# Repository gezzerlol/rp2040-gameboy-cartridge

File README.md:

2 layer pcb version of Shilga's RP2040 Gameboy flash cartridge. Also replaced some components with bigger packages, and easier to find components.

Changes:
-Removed inner layers, instead routed buses and tracks in place of the power planes at the back layer. Also one single signal track is moved to the back layer.
-Replaced 1005 caps with 1608's. JLCPCB doesn't do 1005 package in ecomomic PCBA service.
-Added an optional location for AMS1117-3.3 regulator, in case the MCP1825T isn't available. If AMS1117-3.3 is used, JP2 middle pad solder mask should be removed and soldered to supply a constant POWERGOOD signal that enables the level shifters. 

With these three changes, the PCB could be manufactured at 2$ for 5pcs at JLCPCB. Also if PCBA service is needed, it reduces the number of the extended components that add 3$ of setup fee each. 

The RP2040, TXB0108, TXB0102 and the WS2812b are inevitably extended parts at JLCPCB.

Not tested:
-The whole PCB
-JP2 POWERGOOD bypass functionality(keeping IC's enabled at all times may be a problem)
-Replacement of power planes with tracks
-AMS1117-3.3 compatibility

Goals:
-Replacement of TXB level shifters with discrete circuits made of jellybean transistors. This might be difficult because there are 26 data lines that needs to be level shifted and there is little space, too much moving around might be needed. Heck, might even need to use the back layer.
-Replacement of CJ2302 mosfet with a cheaper one. AO3400A might be a candidate.
-Replacement of the diodes with jellybean ones
-Making the whole pcb made of jellybean parts except RP2040

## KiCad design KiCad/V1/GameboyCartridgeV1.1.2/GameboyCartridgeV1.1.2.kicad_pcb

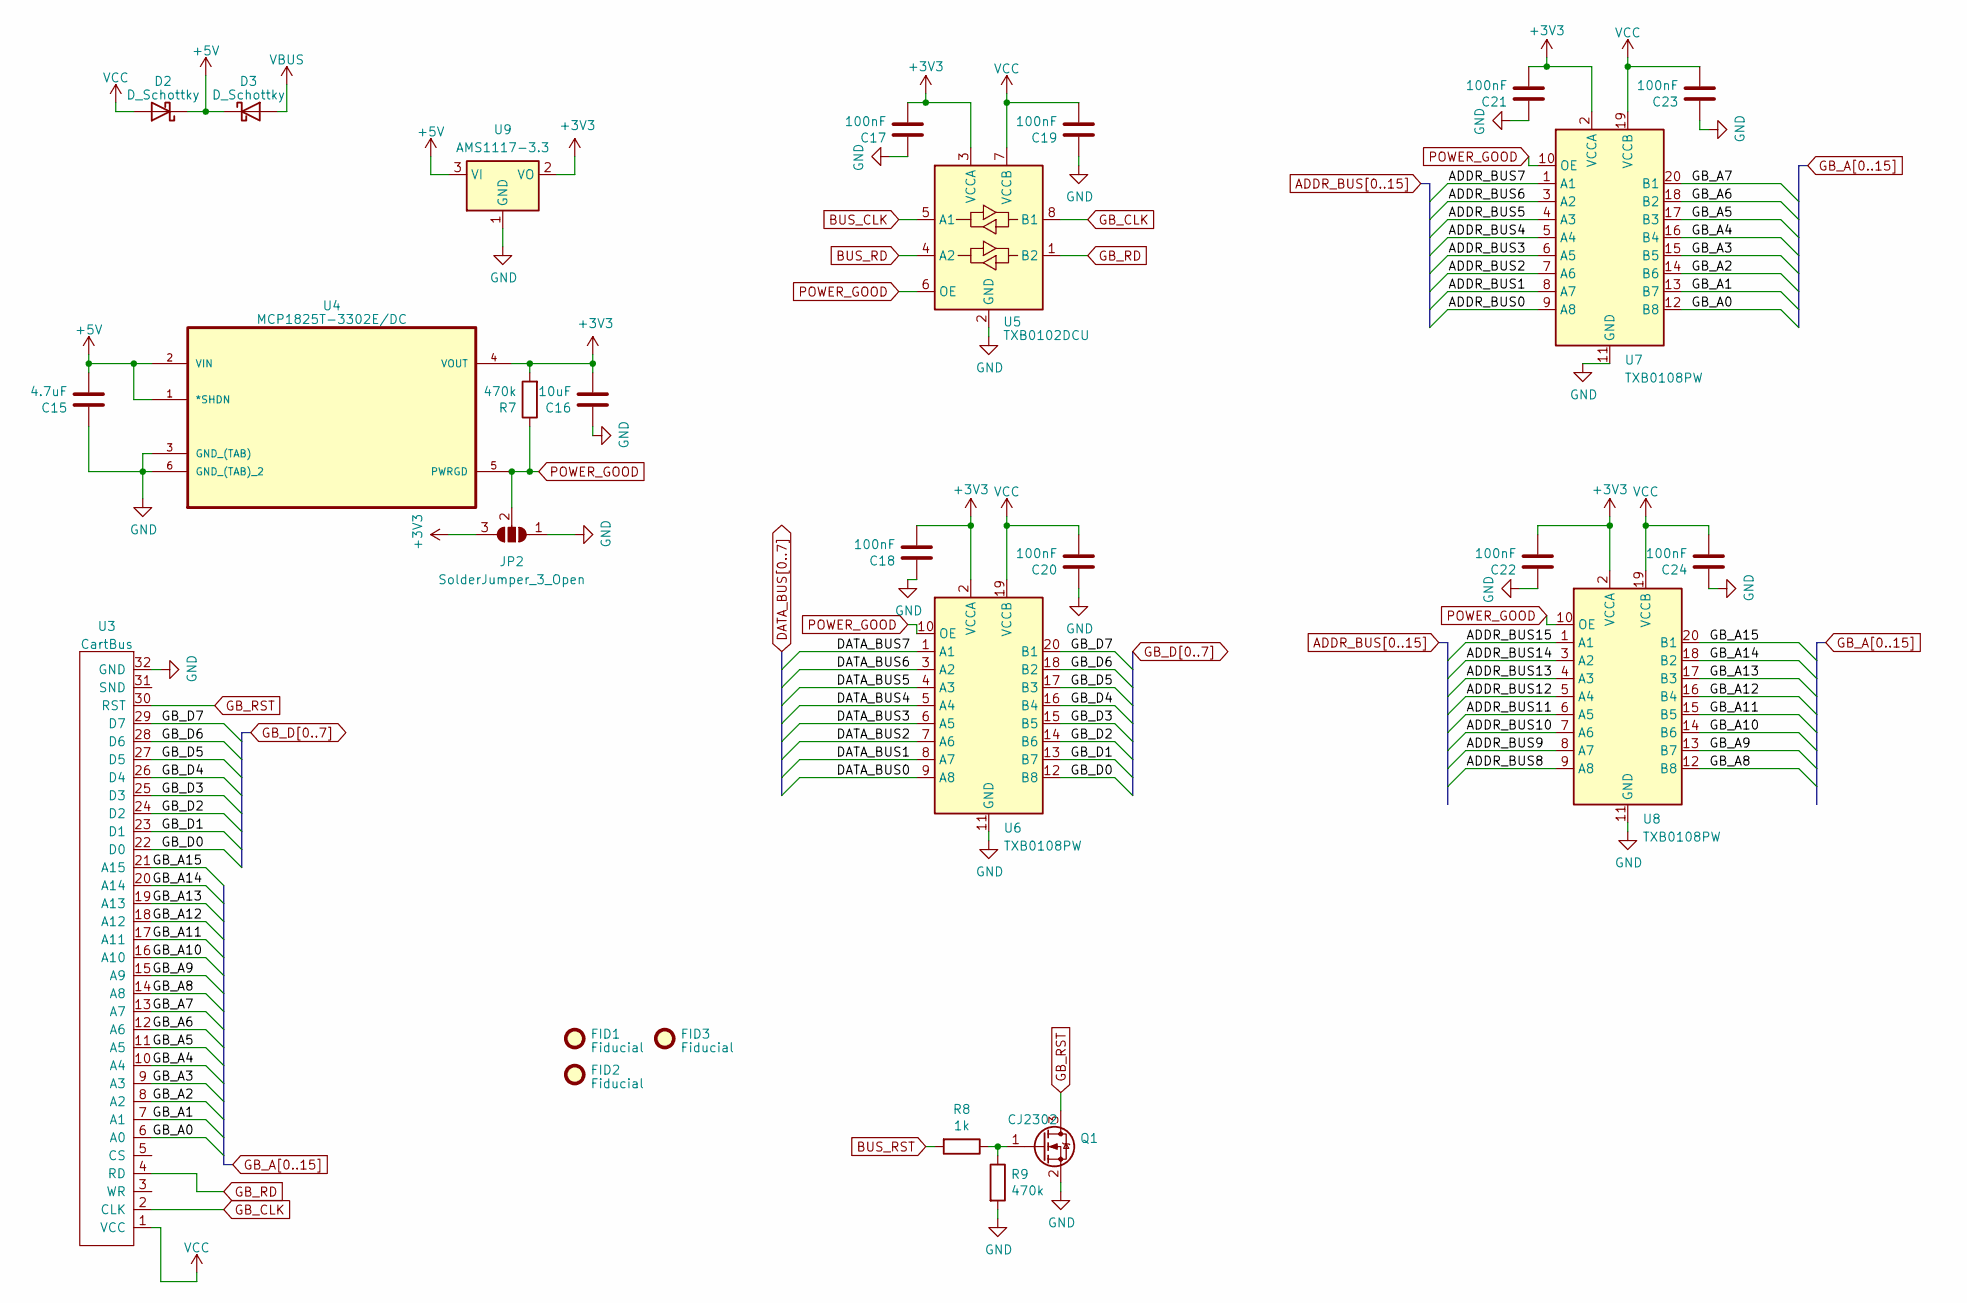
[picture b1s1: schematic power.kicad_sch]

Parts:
C15: 4.7uF; C_0603_1608Metric_Pad1.08x0.95mm_HandSolder
C16: 10uF; C_0603_1608Metric_Pad1.08x0.95mm_HandSolder
C17, C18, C19, C20, C21, C22, C23, C24: 100nF; C_0603_1608Metric_Pad1.08x0.95mm_HandSolder
D2, D3: D_Schottky; D_SOD-123F; LCSC C669022
FID1, FID2, FID3: Fiducial; Fiducial_1mm_Mask2mm
JP2: SolderJumper_3_Open; SolderJumper-3_P1.3mm_Open_RoundedPad1.0x1.5mm_NumberLabels
Q1: CJ2302; SOT-23_Handsoldering; LCSC C8548
R7, R9: 470k; R_0603_1608Metric_Pad0.98x0.95mm_HandSolder
R8: 1k; R_0603_1608Metric_Pad0.98x0.95mm_HandSolder
U3: CartBus; GameBoy_Cartridge_EdgeConnector
U4: MCP1825T-3302E/DC; SOT230P700X180-6N; MPN MCP1825T-3302E/DC; LCSC C632684
U5: TXB0102DCU; VSSOP-8_2.4x2.1mm_P0.5mm; LCSC C60709
U6, U7, U8: TXB0108PW; TSSOP-20_4.4x6.5mm_P0.65mm; LCSC C53406
U9: AMS1117-3.3; SOT-223-3_TabPin2

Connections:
+3V3: C16.2, C17.2, C18.2, C21.2, C22.2, JP2.3 (B), R7.2, U4.4 (VOUT), U5.3 (VCCA), U6.2 (VCCA), U7.2 (VCCA), U8.2 (VCCA), U9.2 (VO); also elsewhere on the board
+5V: C15.2, D2.1 (K), D3.1 (K), U4.1 (*SHDN), U4.2 (VIN), U9.3 (VI)
ADDR_BUS0: U7.9 (A8); also elsewhere on the board
ADDR_BUS1: U7.8 (A7); also elsewhere on the board
ADDR_BUS2: U7.7 (A6); also elsewhere on the board
ADDR_BUS3: U7.6 (A5); also elsewhere on the board
ADDR_BUS4: U7.5 (A4); also elsewhere on the board
ADDR_BUS5: U7.4 (A3); also elsewhere on the board
ADDR_BUS6: U7.3 (A2); also elsewhere on the board
ADDR_BUS7: U7.1 (A1); also elsewhere on the board
ADDR_BUS8: U8.9 (A8); also elsewhere on the board
ADDR_BUS9: U8.8 (A7); also elsewhere on the board
ADDR_BUS10: U8.7 (A6); also elsewhere on the board
ADDR_BUS11: U8.6 (A5); also elsewhere on the board
ADDR_BUS12: U8.5 (A4); also elsewhere on the board
ADDR_BUS13: U8.4 (A3); also elsewhere on the board
ADDR_BUS14: U8.3 (A2); also elsewhere on the board
ADDR_BUS15: U8.1 (A1); also elsewhere on the board
BUS_CLK: U5.5 (A1); also elsewhere on the board
BUS_RD: U5.4 (A2); also elsewhere on the board
BUS_RST: R8.2; also elsewhere on the board
DATA_BUS0: U6.9 (A8); also elsewhere on the board
DATA_BUS1: U6.8 (A7); also elsewhere on the board
DATA_BUS2: U6.7 (A6); also elsewhere on the board
DATA_BUS3: U6.6 (A5); also elsewhere on the board
DATA_BUS4: U6.5 (A4); also elsewhere on the board
DATA_BUS5: U6.4 (A3); also elsewhere on the board
DATA_BUS6: U6.3 (A2); also elsewhere on the board
DATA_BUS7: U6.1 (A1); also elsewhere on the board
GB_A0: U3.6 (A0), U7.12 (B8)
GB_A1: U3.7 (A1), U7.13 (B7)
GB_A2: U3.8 (A2), U7.14 (B6)
GB_A3: U3.9 (A3), U7.15 (B5)
GB_A4: U3.10 (A4), U7.16 (B4)
GB_A5: U3.11 (A5), U7.17 (B3)
GB_A6: U3.12 (A6), U7.18 (B2)
GB_A7: U3.13 (A7), U7.20 (B1)
GB_A8: U3.14 (A8), U8.12 (B8)
GB_A9: U3.15 (A9), U8.13 (B7)
GB_A10: U3.16 (A10), U8.14 (B6)
GB_A11: U3.17 (A11), U8.15 (B5)
GB_A12: U3.18 (A12), U8.16 (B4)
GB_A13: U3.19 (A13), U8.17 (B3)
GB_A14: U3.20 (A14), U8.18 (B2)
GB_A15: U3.21 (A15), U8.20 (B1)
GB_CLK: U3.2 (CLK~), U5.8 (B1)
GB_D0: U3.22 (D0), U6.12 (B8)
GB_D1: U3.23 (D1), U6.13 (B7)
GB_D2: U3.24 (D2), U6.14 (B6)
GB_D3: U3.25 (D3), U6.15 (B5)
GB_D4: U3.26 (D4), U6.16 (B4)
GB_D5: U3.27 (D5), U6.17 (B3)
GB_D6: U3.28 (D6), U6.18 (B2)
GB_D7: U3.29 (D7), U6.20 (B1)
GB_RD: U3.4 (RD), U5.1 (B2)
GB_RST: Q1.3 (D), U3.30 (RST)
GND: C15.1, C16.1, C17.1, C18.1, C19.1, C20.1, C21.1, C22.1, C23.1, C24.1, JP2.1 (A), Q1.2 (S), R9.2, U3.32 (GND), U4.3 (GND_(TAB)), U4.6 (GND_(TAB)_2), U5.2 (GND), U6.11 (GND), U7.11 (GND), U8.11 (GND), U9.1 (GND); also elsewhere on the board
unnamed: Q1.1 (G), R8.1, R9.1
POWER_GOOD: JP2.2 (C), R7.1, U4.5 (PWRGD), U5.6 (OE), U6.10 (OE), U7.10 (OE), U8.10 (OE)
VBUS: D3.2 (A); also elsewhere on the board
VCC: C19.2, C20.2, C23.2, C24.2, D2.2 (A), U3.1 (VCC), U5.7 (VCCB), U6.19 (VCCB), U7.19 (VCCB), U8.19 (VCCB)

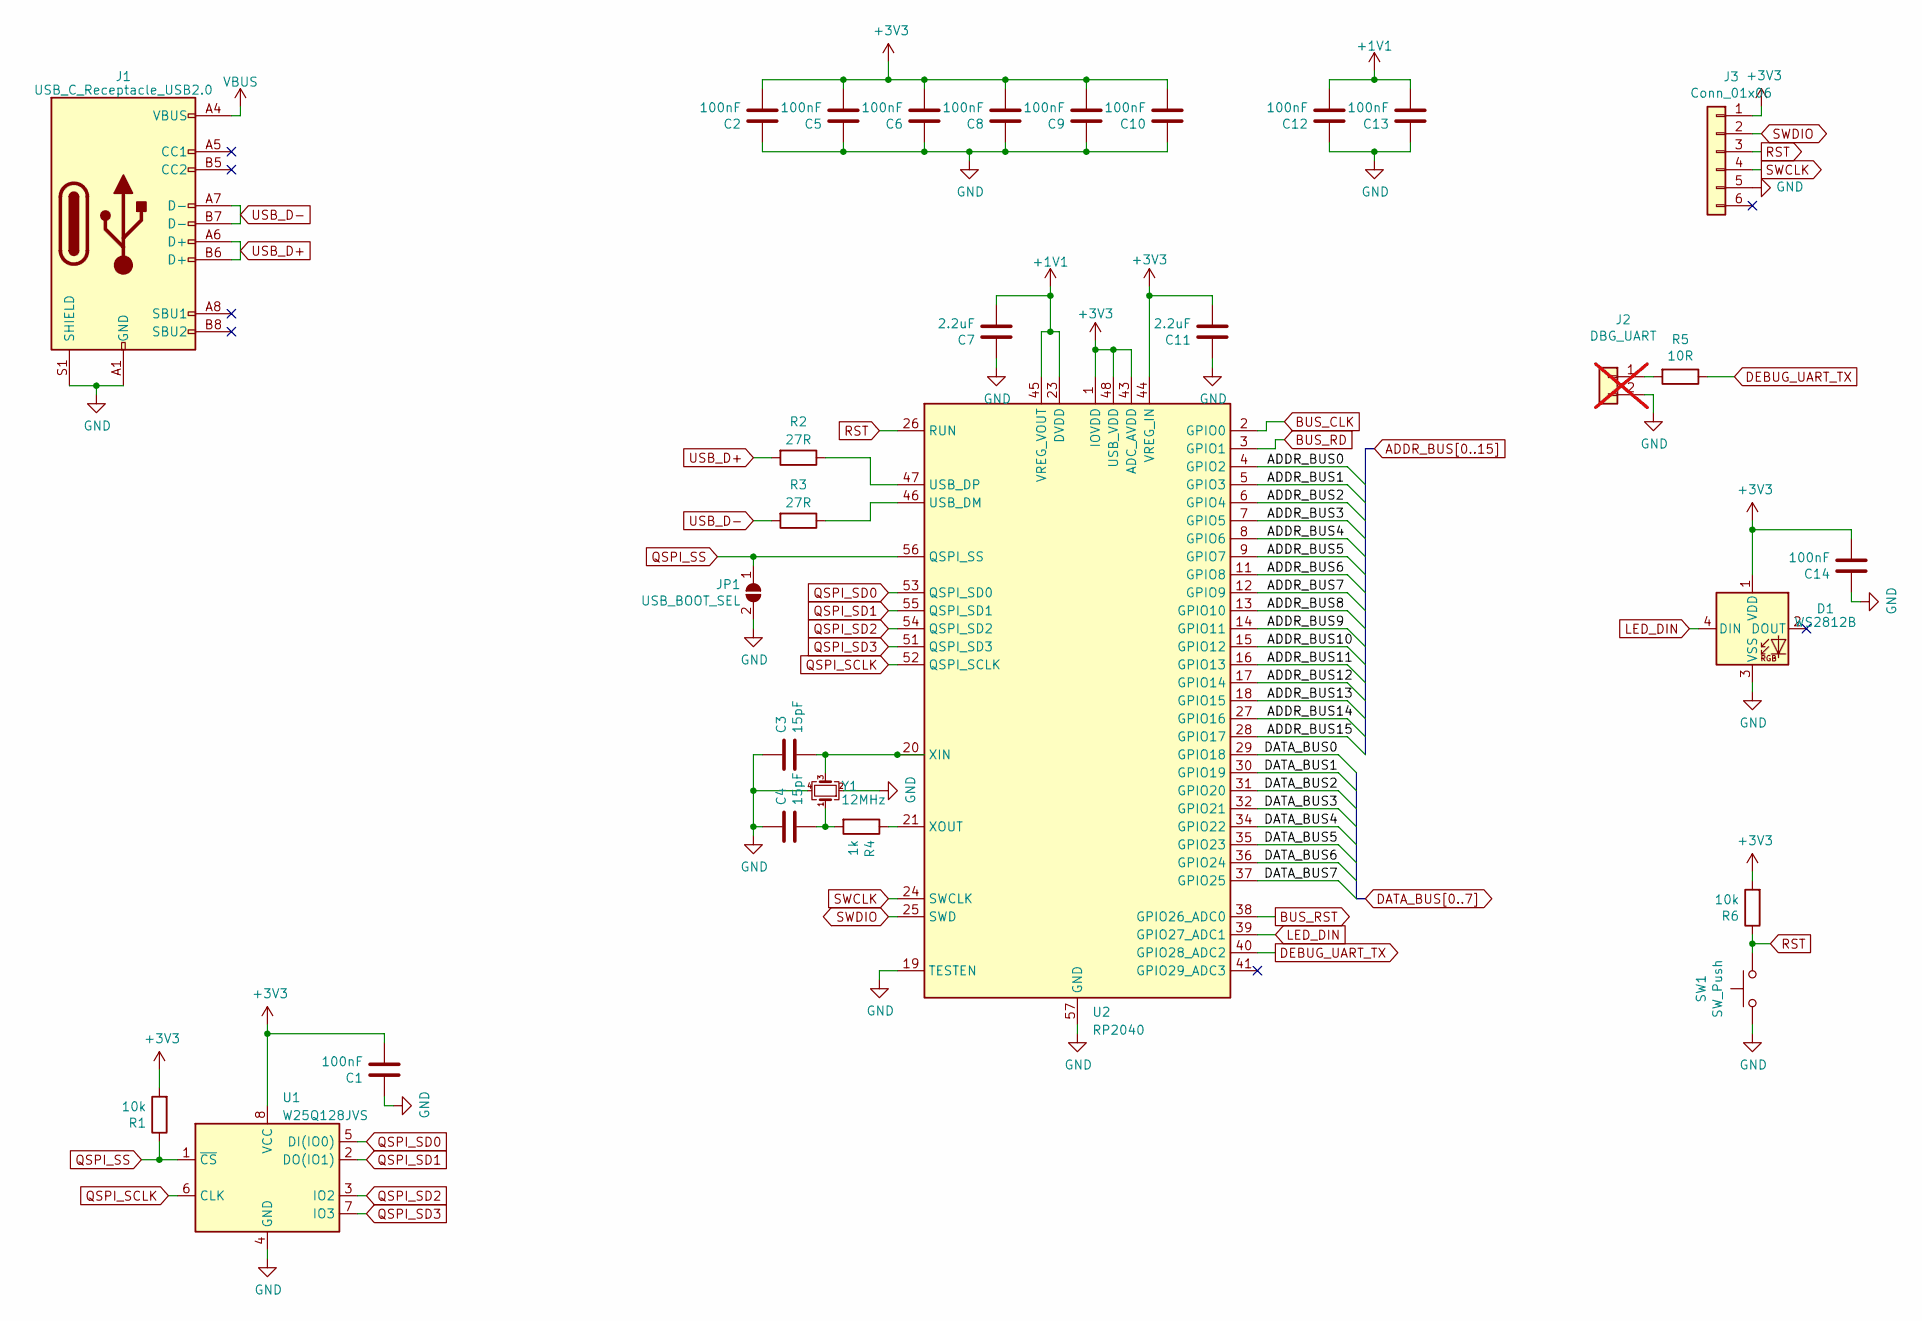
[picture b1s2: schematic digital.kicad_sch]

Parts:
C1, C2, C5, C6, C8, C9, C10, C12, C13, C14: 100nF; C_0603_1608Metric_Pad1.08x0.95mm_HandSolder
C3, C4: 15pF; C_0603_1608Metric_Pad1.08x0.95mm_HandSolder; LCSC C1644
C7, C11: 2.2uF; C_0603_1608Metric_Pad1.08x0.95mm_HandSolder
D1: WS2812B; LED_WS2812B_PLCC4_5.0x5.0mm_P3.2mm; LCSC C2761795
J1: USB_C_Receptacle_USB2.0; USB_C_Receptacle_GCT_USB4105-xx-A_16P_TopMnt_Horizontal; LCSC C2927037
J2: DBG_UART; PinHeader_1x02_P2.54mm_Horizontal; not fitted
J3: Conn_01x06; Tag-Connect_TC2030-IDC-FP_2x03_P1.27mm_Vertical
JP1: USB_BOOT_SEL; SolderJumper-2_P1.3mm_Open_RoundedPad1.0x1.5mm
R1, R6: 10k; R_0603_1608Metric_Pad0.98x0.95mm_HandSolder
R2, R3: 27R; R_0603_1608Metric_Pad0.98x0.95mm_HandSolder
R4: 1k; R_0603_1608Metric_Pad0.98x0.95mm_HandSolder
R5: 10R; R_0603_1608Metric_Pad0.98x0.95mm_HandSolder
SW1: SW_Push; SW_SPST_TL3342; LCSC C2886898
U1: W25Q128JVS; SOIC-8_5.23x5.23mm_P1.27mm; LCSC C97521
U2: RP2040; QFN-56-1EP_7x7mm_P0.4mm_EP3.2x3.2mm; LCSC C2040
Y1: 12MHz; Crystal_SMD_TXC_7M-4Pin_3.2x2.5mm; LCSC C668845

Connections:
+1V1: C7.2, C12.2, C13.2, U2.23 (DVDD), U2.45 (VREG_VOUT), U2.50 (DVDD)
+3V3: C1.2, C2.2, C5.2, C6.2, C8.2, C9.2, C10.2, C11.2, C14.2, D1.1 (VDD), J3.1, R1.2, R6.2, U1.8 (VCC), U2.1 (IOVDD), U2.10 (IOVDD), U2.22 (IOVDD), U2.33 (IOVDD), U2.42 (IOVDD), U2.43 (ADC_AVDD), U2.44 (VREG_IN), U2.48 (USB_VDD), U2.49 (IOVDD); also elsewhere on the board
ADDR_BUS0: U2.4 (GPIO2); also elsewhere on the board
ADDR_BUS1: U2.5 (GPIO3); also elsewhere on the board
ADDR_BUS2: U2.6 (GPIO4); also elsewhere on the board
ADDR_BUS3: U2.7 (GPIO5); also elsewhere on the board
ADDR_BUS4: U2.8 (GPIO6); also elsewhere on the board
ADDR_BUS5: U2.9 (GPIO7); also elsewhere on the board
ADDR_BUS6: U2.11 (GPIO8); also elsewhere on the board
ADDR_BUS7: U2.12 (GPIO9); also elsewhere on the board
ADDR_BUS8: U2.13 (GPIO10); also elsewhere on the board
ADDR_BUS9: U2.14 (GPIO11); also elsewhere on the board
ADDR_BUS10: U2.15 (GPIO12); also elsewhere on the board
ADDR_BUS11: U2.16 (GPIO13); also elsewhere on the board
ADDR_BUS12: U2.17 (GPIO14); also elsewhere on the board
ADDR_BUS13: U2.18 (GPIO15); also elsewhere on the board
ADDR_BUS14: U2.27 (GPIO16); also elsewhere on the board
ADDR_BUS15: U2.28 (GPIO17); also elsewhere on the board
BUS_CLK: U2.2 (GPIO0); also elsewhere on the board
BUS_RD: U2.3 (GPIO1); also elsewhere on the board
BUS_RST: U2.38 (GPIO26_ADC0); also elsewhere on the board
DATA_BUS0: U2.29 (GPIO18); also elsewhere on the board
DATA_BUS1: U2.30 (GPIO19); also elsewhere on the board
DATA_BUS2: U2.31 (GPIO20); also elsewhere on the board
DATA_BUS3: U2.32 (GPIO21); also elsewhere on the board
DATA_BUS4: U2.34 (GPIO22); also elsewhere on the board
DATA_BUS5: U2.35 (GPIO23); also elsewhere on the board
DATA_BUS6: U2.36 (GPIO24); also elsewhere on the board
DATA_BUS7: U2.37 (GPIO25); also elsewhere on the board
DEBUG_UART_TX: R5.1, U2.40 (GPIO28_ADC2)
GND: C1.1, C2.1, C3.1, C4.1, C5.1, C6.1, C7.1, C8.1, C9.1, C10.1, C11.1, C12.1, C13.1, C14.1, D1.3 (VSS), J1.A1 (GND), J1.A12 (GND), J1.B1 (GND), J1.B12 (GND), J1.S1 (SHIELD), J2.2, J3.5, JP1.2 (B), SW1.2, U1.4 (GND), U2.19 (TESTEN), U2.57 (GND), Y1.2, Y1.4; also elsewhere on the board
LED_DIN: D1.4 (DIN), U2.39 (GPIO27_ADC1)
unnamed: C4.2, R4.2, Y1.1
unnamed: J2.1, R5.2
unnamed: R3.1, U2.46 (USB_DM)
unnamed: R2.1, U2.47 (USB_DP)
unnamed: C3.2, U2.20 (XIN), Y1.3
unnamed: R4.1, U2.21 (XOUT)
QSPI_SCLK: U1.6 (CLK), U2.52 (QSPI_SCLK)
QSPI_SD0: U1.5 (DI(IO0)), U2.53 (QSPI_SD0)
QSPI_SD1: U1.2 (DO(IO1)), U2.55 (QSPI_SD1)
QSPI_SD2: U1.3 (IO2), U2.54 (QSPI_SD2)
QSPI_SD3: U1.7 (IO3), U2.51 (QSPI_SD3)
QSPI_SS: JP1.1 (A), R1.1, U1.1 (~CS), U2.56 (QSPI_SS)
RST: J3.3, R6.1, SW1.1, U2.26 (RUN)
SWCLK: J3.4, U2.24 (SWCLK)
SWDIO: J3.2, U2.25 (SWD)
USB_D+: J1.A6 (D+), J1.B6 (D+), R2.2
USB_D-: J1.A7 (D-), J1.B7 (D-), R3.2
VBUS: J1.A4 (VBUS), J1.A9 (VBUS), J1.B4 (VBUS), J1.B9 (VBUS); also elsewhere on the board

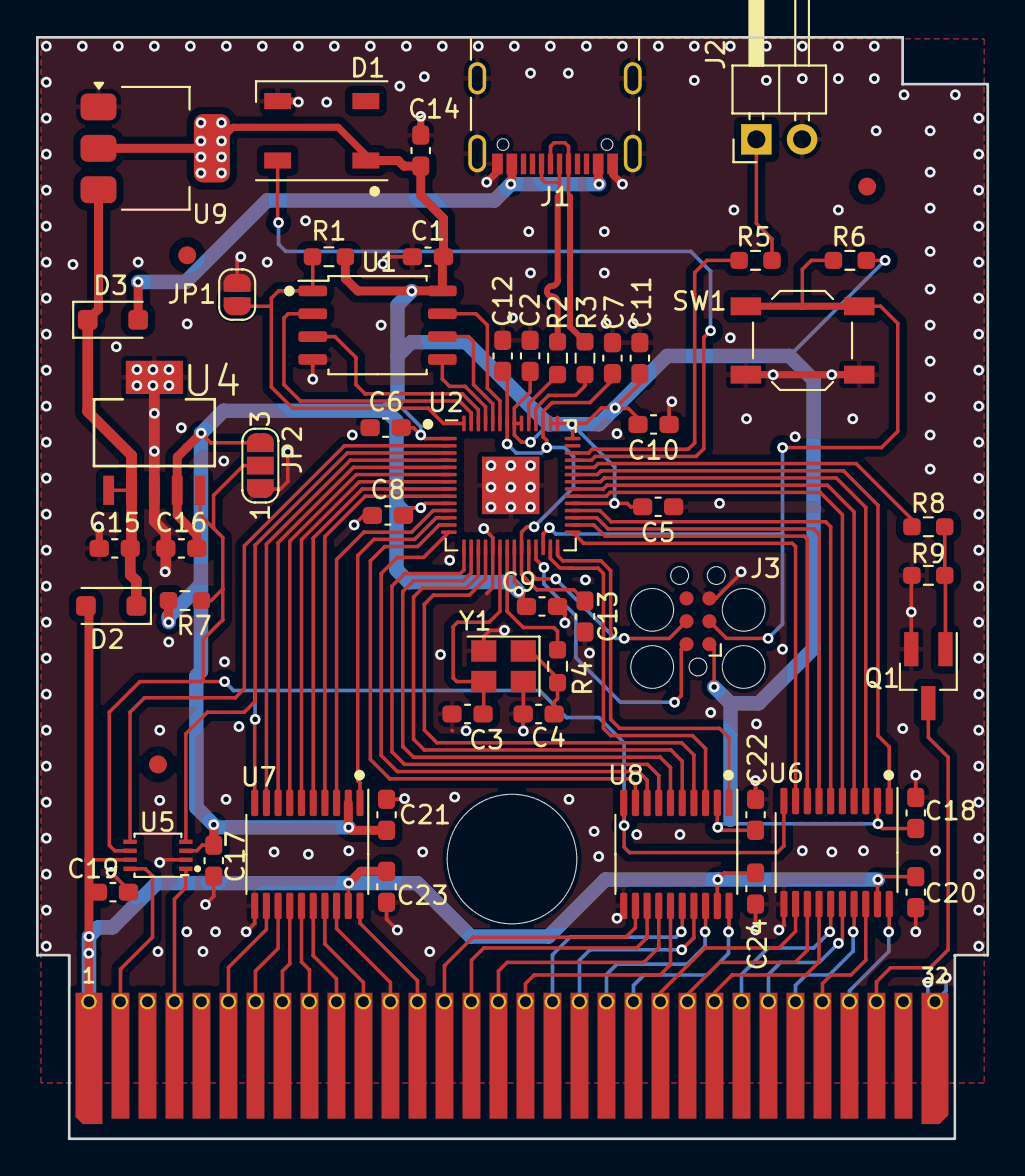
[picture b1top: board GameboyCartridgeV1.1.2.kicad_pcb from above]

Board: 2 copper layers, 52.8 x 61.2 mm, 56 parts (0 on the bottom side), 81 nets.
